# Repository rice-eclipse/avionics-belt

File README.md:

# BELT: Basic Electronics Learning Toolkit

BELT is a simple altimeter PCB intended as a pedagogical device in Rice Eclipse's upcoming electronics hardware educational program, which has been given the provisional nickname "Avionics Certs." 

The development of BELT began in December 2023.

## Components

- **Microcontroller:** Raspberry Pi Pico H ([SC0917](https://www.digikey.com/en/products/detail/raspberry-pi/SC0917/16608257))
- **Barometer:** Infineon Analog Absolute Pressure Sensor ([KP212K1409](https://www.digikey.com/en/products/detail/infineon-technologies/KP212K1409XTMA1/13582301))
- **Thermometer:** Atmel I2C Digital Temperature Sensor ([AT30TS75A](https://www.digikey.com/en/products/detail/microchip-technology/AT30TS75A-SS8M-T/4518713))

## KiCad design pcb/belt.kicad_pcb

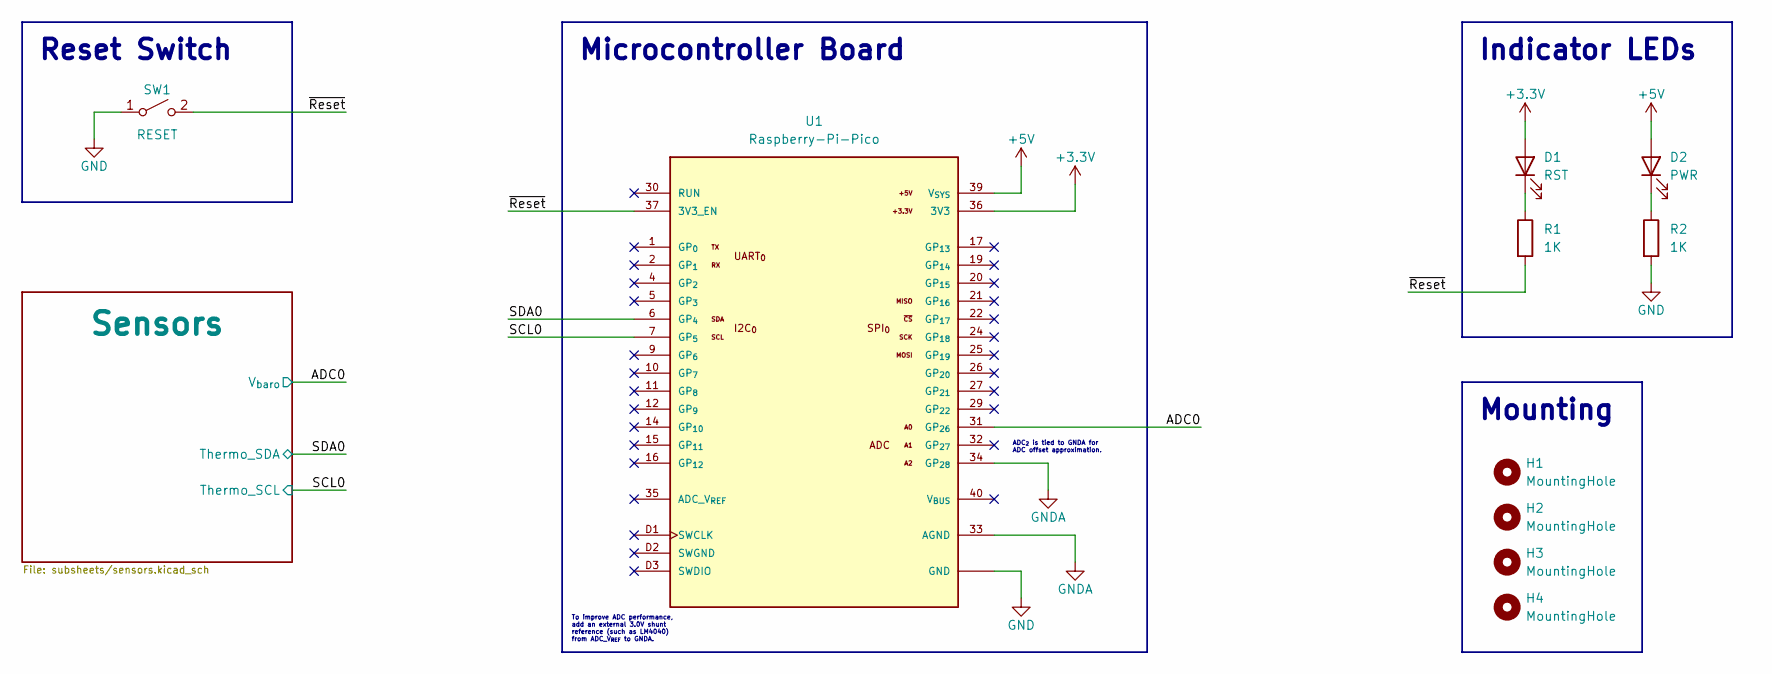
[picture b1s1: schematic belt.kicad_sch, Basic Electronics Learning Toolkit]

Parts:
D1: RST; LED_D5.0mm
D2: PWR; LED_D5.0mm
H1, H2, H3, H4: MountingHole; MountingHole_2.7mm_M2.5
R1, R2: 1K; R_Axial_DIN0207_L6.3mm_D2.5mm_P10.16mm_Horizontal
SW1: RESET; SW_PUSH_6mm_H5mm
U1: Raspberry-Pi-Pico; Part Number SC0915

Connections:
+3.3V: D1.2 (A), U1.36 (3V3); also elsewhere on the board
+5V: D2.2 (A), U1.39 (V_{SYS}); also elsewhere on the board
/ADC0: U1.31 (GP_{26}); also elsewhere on the board
/SCL0: U1.7 (GP_{5}); also elsewhere on the board
/SDA0: U1.6 (GP_{4}); also elsewhere on the board
/~Reset: R1.2, SW1.2 (B), U1.37 (3V3_EN)
GND: R2.2, SW1.1 (A), U1.3 (GND), U1.8 (GND), U1.13 (GND), U1.18 (GND), U1.23 (GND), U1.28 (GND), U1.38 (GND); also elsewhere on the board
GNDA: U1.33 (AGND), U1.34 (GP_{28}); also elsewhere on the board
unnamed: D1.1 (K), R1.1
unnamed: D2.1 (K), R2.1

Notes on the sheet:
Indicator LEDs
Microcontroller Board
Reset Switch
Mounting
To improve ADC performance, add an external 3.0V shunt reference (such as LM4040) from ADC_V_{REF} to GNDA.
ADC_{2} is tied to GNDA for ADC offset approximation.

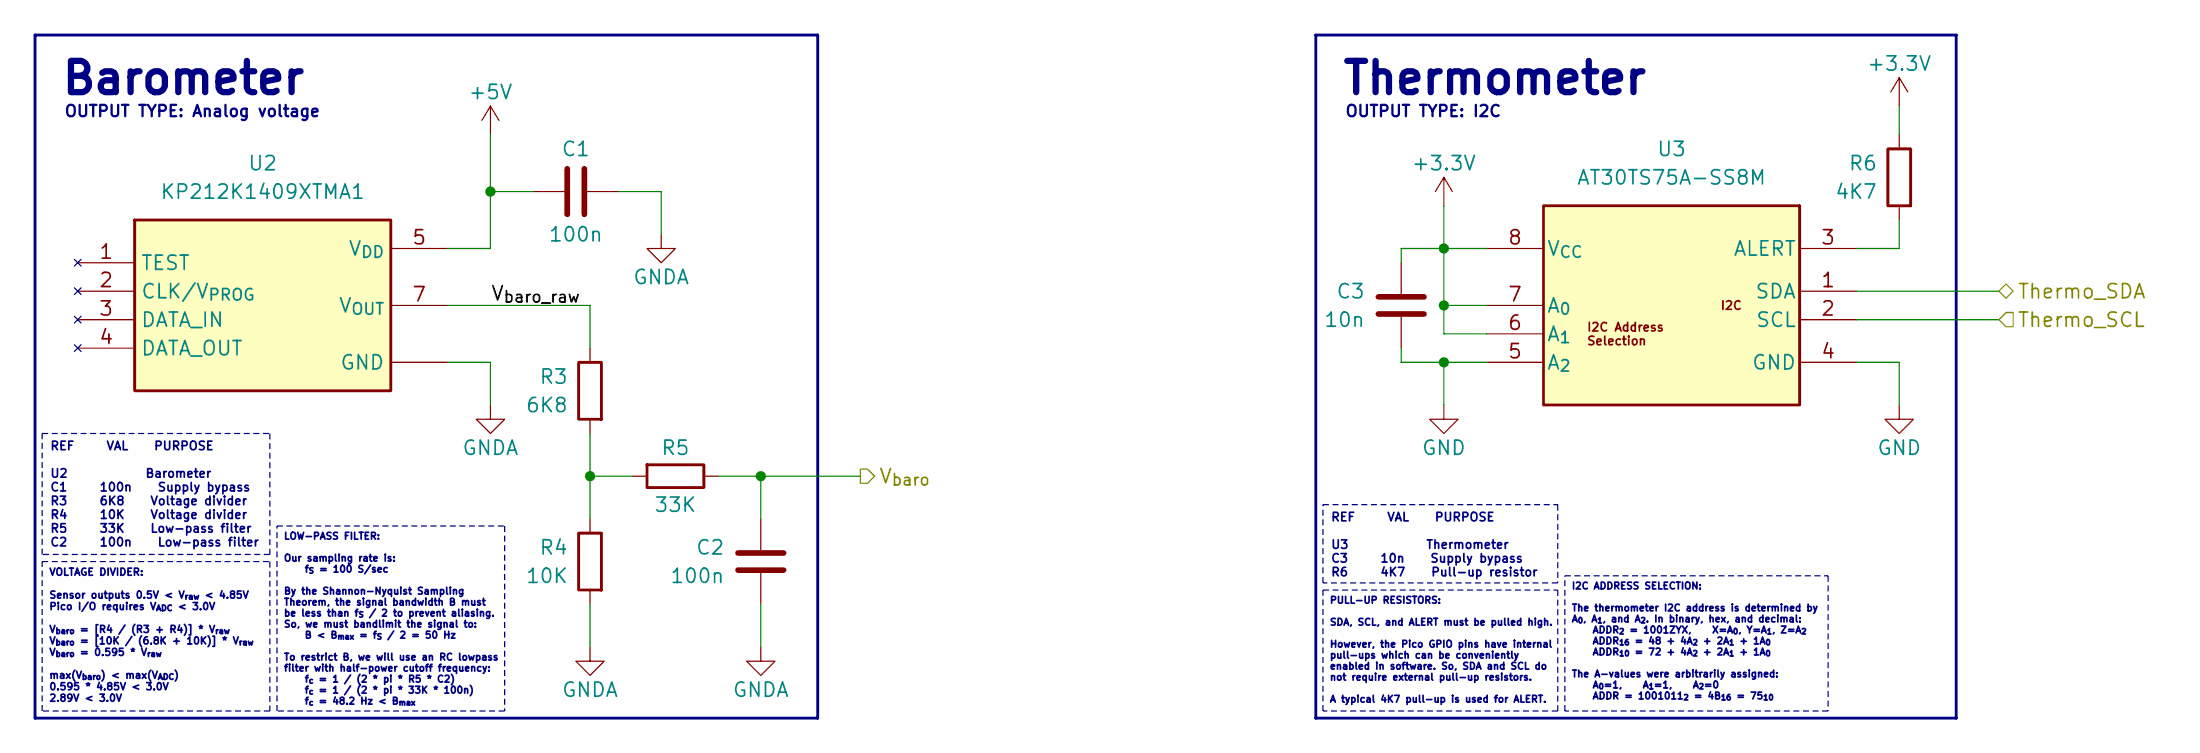
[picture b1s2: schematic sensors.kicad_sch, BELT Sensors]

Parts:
C1, C2: 100n; C_1206_3216Metric_Pad1.33x1.80mm_HandSolder
C3: 10n; C_1206_3216Metric_Pad1.33x1.80mm_HandSolder
R3: 6K8; R_Axial_DIN0207_L6.3mm_D2.5mm_P10.16mm_Horizontal
R4: 10K; R_Axial_DIN0207_L6.3mm_D2.5mm_P10.16mm_Horizontal
R5: 33K; R_Axial_DIN0207_L6.3mm_D2.5mm_P10.16mm_Horizontal
R6: 4K7; R_Axial_DIN0207_L6.3mm_D2.5mm_P10.16mm_Horizontal
U2: KP212K1409XTMA1; Barometer-KP212K1409XTMA1; Part Number KP212K1409XTMA1
U3: AT30TS75A-SS8M; Thermometer-AT30TS75A-SS8M

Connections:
+3.3V: C3.2, R6.1, U3.6 (A_{1}), U3.7 (A_{0}), U3.8 (V_{CC}); also elsewhere on the board
+5V: C1.1, U2.5 (V_{DD}); also elsewhere on the board
/ADC0: C2.1, R5.1; also elsewhere on the board
/SCL0: U3.2 (SCL); also elsewhere on the board
/SDA0: U3.1 (SDA); also elsewhere on the board
/Sensors/V_{baro_raw}: R3.1, U2.7 (V_{OUT})
GND: C3.1, U3.4 (GND), U3.5 (A_{2}); also elsewhere on the board
GNDA: C1.2, C2.2, R4.2, U2.6 (GND), U2.8 (GND); also elsewhere on the board
unnamed: R3.2, R4.1, R5.2
unnamed: R6.2, U3.3 (ALERT)

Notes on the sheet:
Thermometer
VOLTAGE DIVIDER: Sensor outputs 0.5V < V_{raw} < 4.85V Pico I/O requires V_{ADC} < 3.0V V_{baro} = [R4 / (R3 + R4)] * V_{raw} V_{baro} = [10K / (6.8K + 10K)] * V_{raw} V_{baro} = 0.595 * V_{raw} max(V_{baro}) < max(V_{ADC}) 0.595 * 4.85V < 3.0V 2.89V < 3.0V
REF VAL PURPOSE U2 Barometer C1 100n Supply bypass R3 6K8 Voltage divider R4 10K Voltage divider R5 33K Low-pass filter C2 100n Low-pass filter
Barometer
REF VAL PURPOSE U3 Thermometer C3 10n Supply bypass R6 4K7 Pull-up resistor
PULL-UP RESISTORS: SDA, SCL, and ALERT must be pulled high. However, the Pico GPIO pins have internal pull-ups which can be conveniently enabled in software. So, SDA and SCL do not require external pull-up resistors. A typical 4K7 pull-up is used for ALERT.
I2C ADDRESS SELECTION: The thermometer I2C address is determined by A_{0}, A_{1}, and A_{2}. In binary, hex, and decimal: ADDR_{2} = 1001ZYX, X=A_{0}, Y=A_{1}, Z=A_{2} ADDR_{16} = 48 + 4A_{2} + 2A_{1} + 1A_{0} ADDR_{10} = 72 + 4A_{2} + 2A_{1} + 1A_{0} The A-values were arbitrarily assigned: A_{0}=1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
LOW-PASS FILTER: Our sampling rate is: f_{S} = 100 S/sec By the Shannon-Nyquist Sampling Theorem, the signal bandwidth B must be less than f_{S} / 2 to prevent aliasing. So, we must bandlimit the signal to: B < B_{max} = f_{S} / 2 = 50 Hz To restrict B, we will use an RC lowpass filter with half-po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
OUTPUT TYPE: I2C
OUTPUT TYPE: Analog voltage

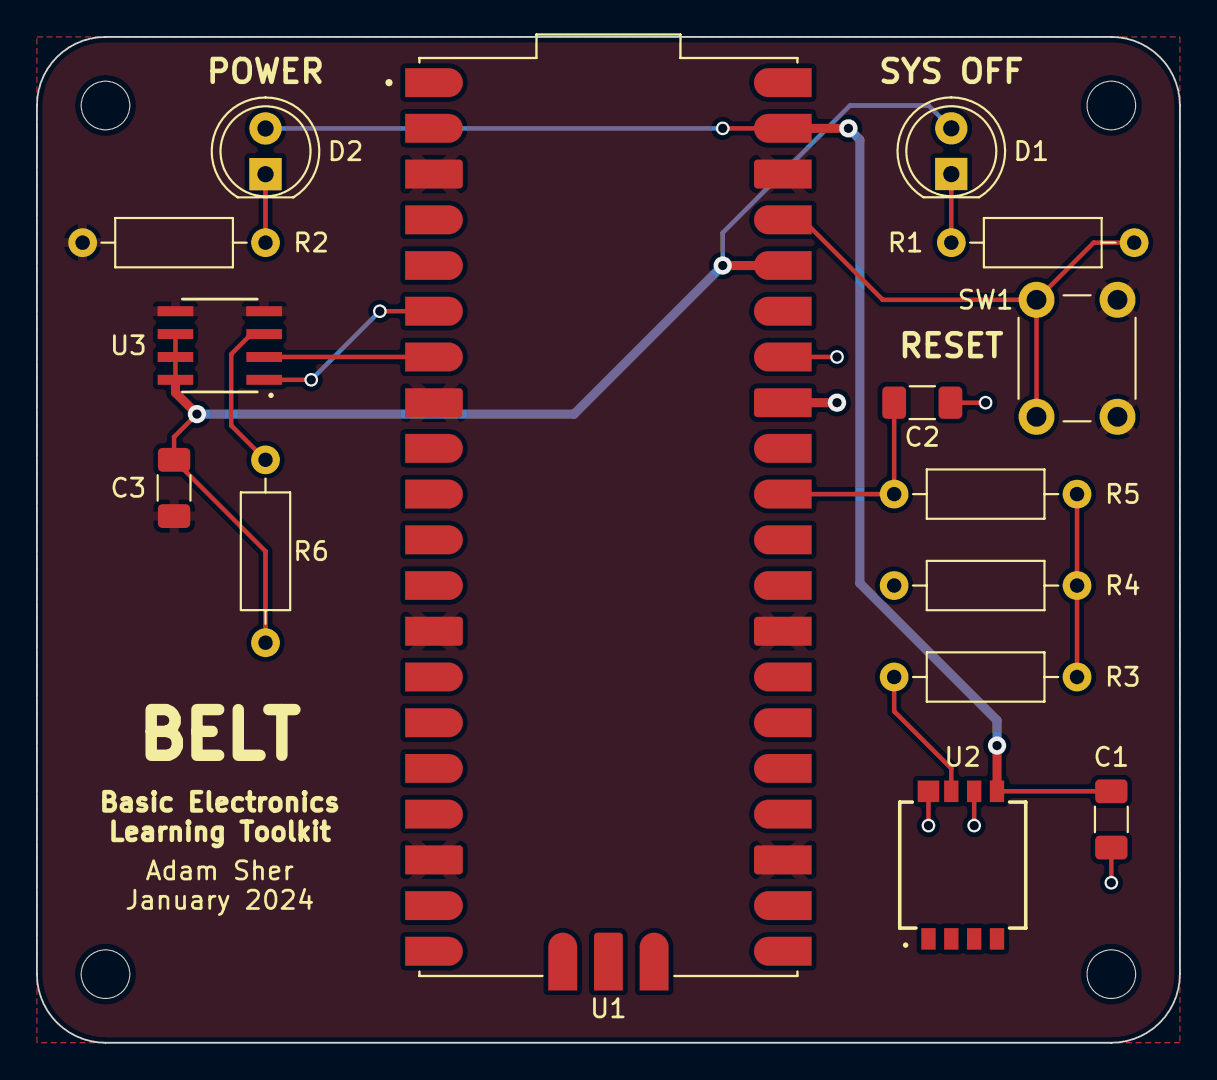
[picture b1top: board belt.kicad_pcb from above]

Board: 2 copper layers, 63.5 x 55.9 mm, 19 parts (0 on the bottom side), 13 nets.

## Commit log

2023-12-26 added raspi and barometer libraries
2023-12-26 added thermometer
2023-12-26 wired things up
2023-12-27 added voltdivs and schematic pages
2023-12-27 renamed dirs
2023-12-31 added new thermometer and fixed symbols
2023-12-31 fixed everything (ERC is no longer mad)
2023-12-31 fixed all the resistors
2024-01-02 mostly finished schematic
2024-01-02 finished schematic v0.3
2024-01-03 modified footprints
2024-01-03 ready for layout
2024-01-03 completed initial layout
